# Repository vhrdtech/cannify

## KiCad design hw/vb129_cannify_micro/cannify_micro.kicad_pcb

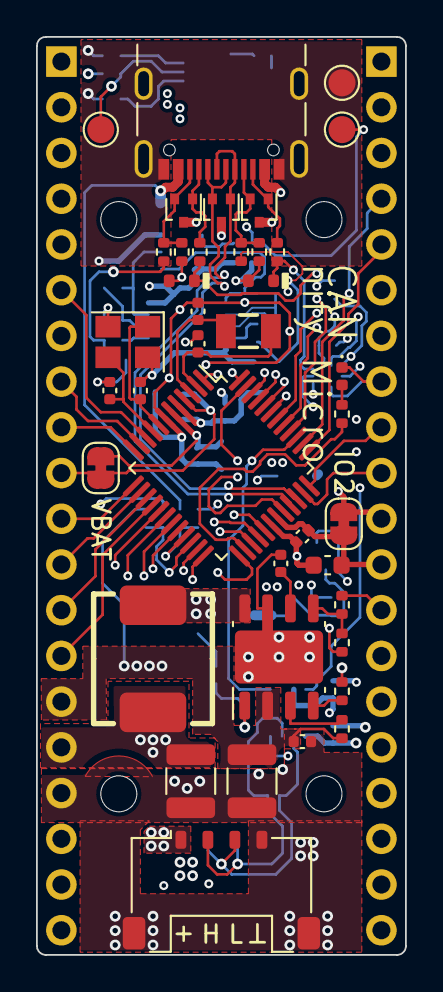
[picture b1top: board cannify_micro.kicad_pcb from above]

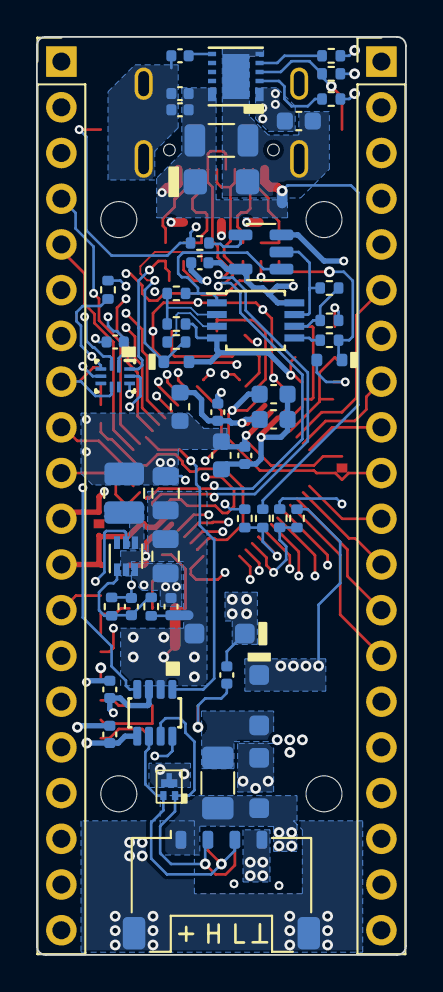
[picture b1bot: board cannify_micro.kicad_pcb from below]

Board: 6 copper layers, 20.5 x 51.0 mm, 98 parts (55 on the bottom side), 83 nets.

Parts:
C1, C2: 10nF; C_0402_1005Metric
C5: 10uF; C_1210_3225Metric
C6, C7, C8, C11, C17, C18, C19, C22, C23, C24, C27: 100nF; C_0402_1005Metric
C9: 100uF; C_1210_3225Metric
C10, C13: 10uF; C_0805_2012Metric
C12: DNP; C_0402_1005Metric
C14: 10uF; C_1206_3216Metric
C15: 3.3nF; C_0402_1005Metric
C16: DNP; C_0603_1608Metric
C20, C25: 4.7uF; C_0603_1608Metric
C21, C31: 24pF; C_0402_1005Metric
C26, C28: 1uF; C_0603_1608Metric
C29, C30: 12pF; C_0402_1005Metric
D1, D2, D3: ESD; SOT-416
D4: Vbr=24V Vcl=35V; D_SMF
D5, D12: Schottky 3A; D_SOD-123F
D6, D7, D8, D9: 5V6; D_SOD-523
D10: PESD2CANFD24V-QBZ; DFN1110D-3_3-XDFN
D11: Vbr=56V; TVS_SOD-123F
D14: LED; LED_0402_1005Metric
F1: 4A Slow blow; Fuse_1206_3216Metric
FB1: MH1608-601Y; L_0603_1608Metric
H1, H2, H3, H4: MountingHole; MountingHole_2.2mm_M2
J1, J2: Conn_01x20; PinHeader_1x20_P2.54mm_Vertical
J3: USB_C_Receptacle_USB2.0; USB_C_Receptacle_GCT_USB4105-xx-A_16P_TopMnt_Horizontal
J4, J5: Pico-Lock 4P; Molex_Pico-Lock_504050-0491_1x04-1MP_P1.50mm_Horizontal
JP2, JP3: Jumper (Short); SolderJumper-2_P1.3mm_Bridged_RoundedPad1.0x1.5mm
L1: LMLP07A7M8R2DTAS; LMLP07A7
L2: DFE252010F-1R0M=P2; L_1008_2520Metric
R1, R2, R18, R19, R20, R21: 5K1; R_0402_1005Metric
R3: 16K2; R_0402_1005Metric
R4, R27, R31: 1K69; R_0402_1005Metric
R5: 49K9; R_0402_1005Metric
R6, R8, R23, R24, R28: 10K; R_0402_1005Metric
R7: 57K6; R_0402_1005Metric
R10: 45k; R_0402_1005Metric
R11: 10k; R_0402_1005Metric
R12, R25: 0; R_0402_1005Metric
R13: 301K; R_0402_1005Metric
R14: 100K; R_0402_1005Metric
R15, R16, R17, R22: 200; R_0402_1005Metric
R30: 39K2; R_0402_1005Metric
TP1, TP2, TP5: TestPoint_Probe; TestPoint_Pad_D1.5mm
U1: STM32G0B1CETxN; LQFP-48_7x7mm_P0.5mm
U2: LV14360SDDAR; SOIC-8-1EP_TI_NOVIA
U3: RT5760; SOT-563
U4: AOZ1376DI-02; DFN-12-AOZ
U5: LMV358A; TSSOP-8_3x3mm_P0.65mm
U6: 74LVC1G08; SOT-23-5
U7: TS3A5223RSWR; RSW0010A
U8: TCAN1044VDDF; TSOT23-6-TI-DDF0008A
Y1: 32.768kHz; ECX-.327-CDX-1293
Y2: 12MHz; Crystal_SMD_3225-4Pin_3.2x2.5mm

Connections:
+3V3_DCDC: C12.1, C13.1, C17.1, C18.1, C19.1, C20.1, C23.1, FB1.1, J2.11, JP2.1 (A), JP3.2 (B), L2.2, R10.2, U1.6 (VDD), U5.8 (V+), U6.5 (VCC), U7.1 (VCC), U8.5 (VIO)
+5V0_DCDC: C9.1, C10.1, C11.1, C16.1, C22.1, J1.16, L1.2, R7.2, R14.2, U3.3 (VIN), U3.5 (EN), U4.1 (VOUT), U4.2 (VOUT), U8.3 (VCC)
+VIN_CAN: C5.1, C6.1, D12.1 (K), J1.15, R6.1, R30.1, U2.2 (VIN)
+VIN_USB: C1.1, C2.1, C14.1, D4.1 (A1), J3.A4 (VBUS), J3.A9 (VBUS), J3.B4 (VBUS), J3.B9 (VBUS), R3.1, U4.11 (VIN), U4.12 (VIN)
/3V3_FB: C12.2, R10.1, R11.2, U3.1 (FB)
/3V3_SW: L2.1, U3.4 (SW)
/+VCAN_F: D12.2 (A), F1.2
/+VCAN_J: D11.2 (A2), F1.1, J4.1, J5.1
/+VDDIO2: C24.1, C25.1, J2.12, JP3.1 (A), U1.31 (VDDIO2)
/AOZ_ENB: R12.1, U4.5 (ENB)
/AOZ_POVP: R13.1, U4.3 (POVP)
/AOZ_SS: C15.1, U4.7 (SS)
/CANH: D10.1 (A1), J4.2, J5.2, U8.7 (CANH)
/CANL: D10.2 (A2), J4.3, J5.3, U8.6 (CANL)
/CAN_STBY: U1.1 (PC13), U8.8 (STB)
/CAN_VDIV: R30.2, R31.1, U1.22 (PB10)
/CC1: D2.2 (K2), J3.A5 (CC1), R1.2, R15.1
/CC1_PR: D6.1 (K), R15.2, R18.1
/CC2: D1.2 (K2), J3.B5 (CC2), R2.2, R16.1
/CC2_PR: D7.1 (K), R16.2, R20.1
/FDCAN_RX: U1.47 (PB8), U8.4 (RXD)
/FDCAN_TX: U1.39 (PD1), U8.1 (TXD)
/HF_OSC_IN: C31.1, U1.8 (PF0), Y2.1
/HF_OSC_OUT: C21.1, U1.9 (PF1), Y2.3
/LED: R27.2, U1.26 (PB14)
/LF_OSC_IN: C29.1, U1.2 (PC14), Y1.1
/LF_OSC_OUT: C30.1, U1.3 (PC15), Y1.2
/LV_BOOT: C8.1, U2.1 (BOOT)
/LV_EN: R6.2, U2.3 (EN)
/LV_FB: R7.1, R8.2, U2.5 (FB)
/LV_RT: R5.1, U2.4 (RT/SYNC)
/LV_SS: C7.1, U2.6 (SS)
/LV_SW: C8.2, D5.1 (K), L1.1, U2.8 (SW)
/PA0: J1.8, U1.11 (PA0)
/PA1: J1.9, U1.12 (PA1)
/PA2: J1.11, U1.13 (PA2)
/PA3: J1.12, U1.14 (PA3)
/PA4: J1.13, U1.15 (PA4)
/PA5: J1.14, U1.16 (PA5)
/PA6: J1.18, U1.17 (PA6)
/PA7: J1.19, U1.18 (PA7)
/PA8: J2.15, U1.28 (PA8)
/PA9: J2.14, U1.29 (PA9/UCPD1_DBCC1)
/PA10: J2.6, U1.32 (PA10/UCPD1_DBCC2)
/PA15: J2.5, U1.37 (PA15)
/PB0: J1.20, U1.19 (PB0)
/PB1: J2.20, U1.20 (PB1)
/PB3: J2.1, U1.42 (PB3)
/PB4: J1.1, U1.43 (PB4)
/PB5: J1.2, U1.44 (PB5)
/PB6: J1.3, U1.45 (PB6)
/PB7: J1.4, U1.46 (PB7)
/PB9: J1.5, U1.48 (PB9)
/PB11: J2.19, U1.23 (PB11)
/PB12: J2.18, U1.24 (PB12)
/PB13: J2.17, U1.25 (PB13)
/PB15: J2.16, U1.27 (PB15)
/PD0: J2.4, U1.38 (PD0)
/PD2: J2.3, U1.40 (PD2)
/PD3: J2.2, U1.41 (PD3)
/PF2_NRST: J1.6, U1.10 (PF2)
/SBU1: D1.1 (K1), J3.A8 (SBU1), R17.1
/SBU1_PR: D8.1 (K), R17.2, U7.2 (NO1)
/SBU2: D2.1 (K1), J3.B8 (SBU2), R22.1
/SBU2_PR: D9.1 (K), R22.2, U7.10 (NO2)
/SWCLK: J2.9, R28.2, U1.36 (PA14), U7.3 (COM1)
/SWDIO: J2.10, U1.35 (PA13), U7.9 (COM2)
/SWD_SEL: R25.2, TP1.1, U7.4 (SEL1), U7.8 (SEL2)
/USB_N: D3.1 (K1), J3.A7 (D-), J3.B7 (D-), U1.33 (PA11/PA9)
/USB_P: D3.2 (K2), J3.A6 (D+), J3.B6 (D+), U1.34 (PA12/PA10)
/USB_VDIV: R3.2, R4.1, U1.21 (PB2)
/VBAT: C26.1, J1.10, JP2.2 (B), U1.4 (VBAT)
/VUSB_FLTB: R14.1, TP2.1, U4.4 (FLTB)
GND: C1.2, C2.2, C5.2, C6.2, C7.2, C9.2, C10.2, C11.2, C13.2, C14.2, C15.2, C16.2, C17.2, C18.2, C19.2, C20.2, C21.2, C22.2, C23.2, C24.2, C25.2, C26.2, C27.2, C28.2, C29.2, C30.2, C31.2, D1.3 (A), D2.3 (A), D3.3 (A), D4.2 (A2), D5.2 (A), D6.2 (A), D7.2 (A), D8.2 (A), D9.2 (A), D10.3 (common), D11.1 (A1), D14.1 (K), J1.7, J1.17, J2.8, J2.13, J3.A1 (GND), J3.A12 (GND), J3.B1 (GND), J3.B12 (GND), J3.S1 (SHIELD), J4.4, J4.MP (MountPin), J5.4, J5.MP (MountPin), R1.1, R2.1, R4.2, R5.2, R8.1, R11.1, R12.2, R13.2, R19.1, R21.1, R28.1, R31.2, TP5.1, U1.7 (VSS), U1.30 (VSS), U2.7 (GND), U2.9 (EPAD_GND), U3.2 (GND), U4.6 (GND), U4.13 (EP_GND), U5.4 (V-), U6.3 (GND), U7.6 (GND), U8.2 (GND), Y2.2, Y2.4
unnamed: D14.2 (A), R27.1
unnamed: R23.2, U5.1, U6.1
unnamed: R24.2, U5.7, U6.2
unnamed: R25.1, U6.4
unnamed: C27.1, C28.1, FB1.2, U1.5 (VREF+)
unnamed: R18.2, U5.3 (+)
unnamed: R19.2, R23.1, U5.2 (-)
unnamed: R20.2, U5.5 (+)
unnamed: R21.2, R24.1, U5.6 (-)

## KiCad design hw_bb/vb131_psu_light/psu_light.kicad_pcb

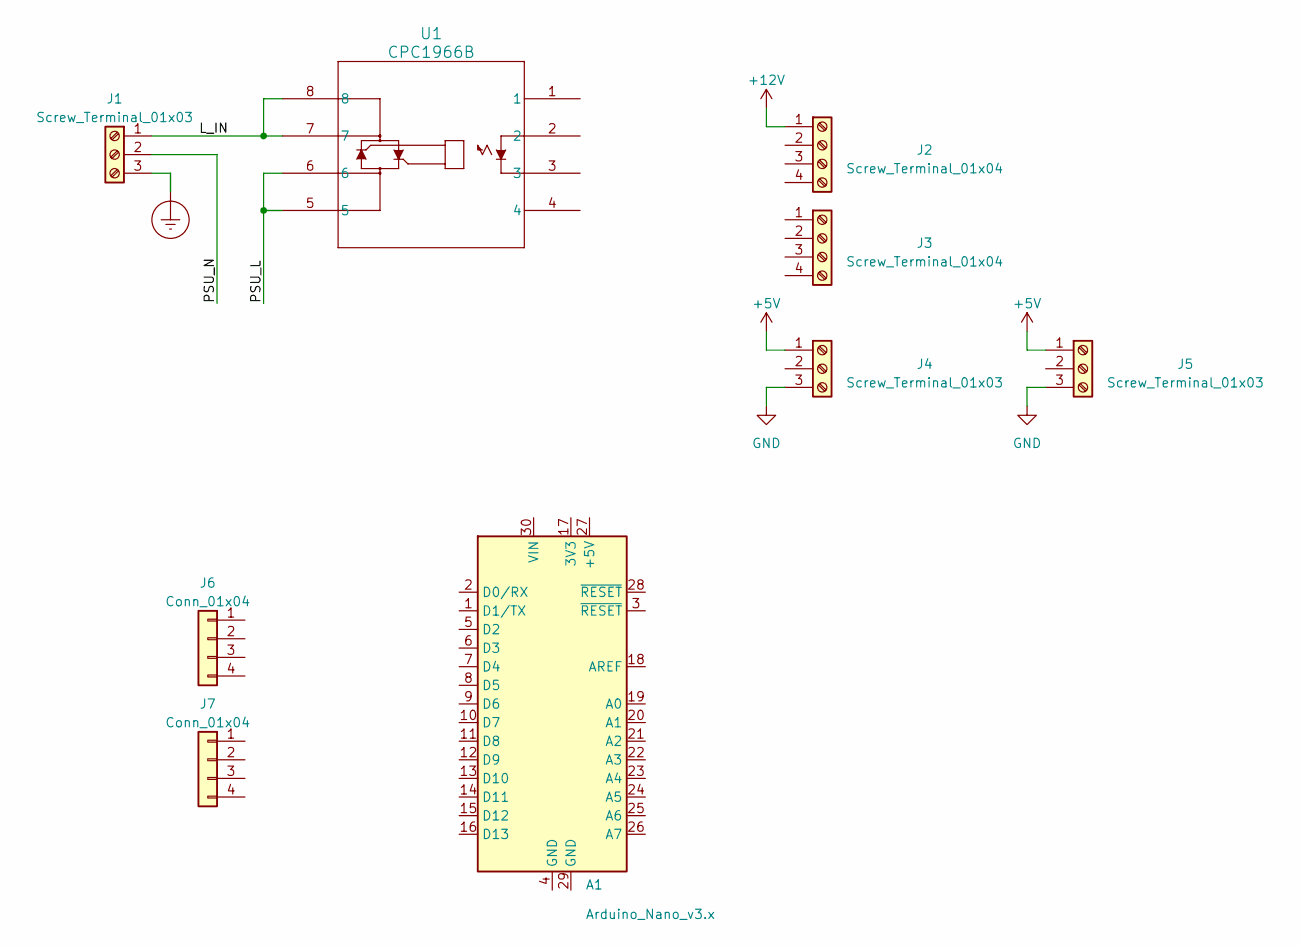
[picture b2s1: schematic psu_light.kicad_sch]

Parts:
A1: Arduino_Nano_v3.x; Arduino_Nano
J1: Screw_Terminal_01x03; TerminalBlock_Phoenix_PT-1,5-3-5.0-H_1x03_P5.00mm_Horizontal
J2, J3: Screw_Terminal_01x04; TerminalBlock_Phoenix_PT-1,5-4-3.5-H_1x04_P3.50mm_Horizontal
J4, J5: Screw_Terminal_01x03; TerminalBlock_Phoenix_PT-1,5-3-3.5-H_1x03_P3.50mm_Horizontal
J6, J7: Conn_01x04; Molex_Nano-Fit_105309-xx04_1x04_P2.50mm_Vertical
U1: CPC1966B; CPC1966B_IXYS-M

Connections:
+5V: J4.1, J5.1
+12V: J2.1
/L_IN: J1.1, U1.7, U1.8
/PSU_L: U1.5, U1.6
/PSU_N: J1.2
Earth_Protective: J1.3
GND: J4.3, J5.3

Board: 2 copper layers, 9 parts (0 on the bottom side), 4 nets, no tracks yet.

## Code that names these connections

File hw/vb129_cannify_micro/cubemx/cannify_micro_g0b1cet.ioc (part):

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Mcu.Name=STM32G0B1C(B-C-E)TxN
Mcu.Package=LQFP48
Mcu.UserName=STM32G0B1CETxN
PA10.Mode=EnableDeadBattery
PA10.Signal=UCPD1_DBCC2
PA11\ [PA9].Mode=Device
PA11\ [PA9].Signal=USB_DM
PA12\ [PA10].Mode=Device
PA12\ [PA10].Signal=USB_DP
PA13.Mode=Serial_Wire
PA13.Signal=SYS_SWDIO
PA14-BOOT0.Mode=Serial_Wire
PA14-BOOT0.Signal=SYS_SWCLK
PA15.Mode=Clock-out-2
PA15.Signal=RCC_MCO_2
PA8.Mode=Dual_Role_AllSignals
PA8.Signal=UCPD1_CC1
PA9.Mode=EnableDeadBattery
PA9.Signal=UCPD1_DBCC1
PB10.GPIOParameters=GPIO_Label
PB10.GPIO_Label=CAN_VDIV
PB10.Mode=IN11
PB10.Signal=ADC1_IN11
PB13.GPIOParameters=GPIO_Label
PB13.GPIO_Label=VUSB_FLTB
PB13.Signal=GPIO_Input
PB14.GPIOParameters=GPIO_Label
PB14.GPIO_Label=LED
PB14.Signal=S_TIM15_CH1
PB15.Mode=Dual_Role_AllSignals
PB15.Signal=UCPD1_CC2
PB2.GPIOParameters=GPIO_Label
PB2.GPIO_Label=USB_VDIV
PB2.Mode=IN10
PB2.Signal=ADC1_IN10
PC13.GPIOParameters=GPIO_Label
PC13.GPIO_Label=CAN_STBY
PC13.Signal=GPIO_Output
PC14-OSC32_IN\ (PC14).Mode=LSE-External-Oscillator
PC14-OSC32_IN\ (PC14).Signal=RCC_OSC32_IN
PC15-OSC32_OUT\ (PC15).Mode=LSE-External-Oscillator
PC15-OSC32_OUT\ (PC15).Signal=RCC_OSC32_OUT
PD0.Mode=FDCAN_Activate
PD0.Signal=FDCAN1_RX
PD1.Mode=FDCAN_Activate
PD1.Signal=FDCAN1_TX
PD3.GPIOParameters=GPIO_Label
PD3.GPIO_Label=NC
PD3.Signal=GPIO_Input
PF0-OSC_IN\ (PF0).Mode=HSE-External-Oscillator
PF0-OSC_IN\ (PF0).Signal=RCC_OSC_IN
PF1-OSC_OUT\ (PF1).Mode=HSE-External-Oscillator
PF1-OSC_OUT\ (PF1).Signal=RCC_OSC_OUT
RCC.HSE_VALUE=8000000
RCC.SYSCLKFreq_VALUE=16000000
board=custom

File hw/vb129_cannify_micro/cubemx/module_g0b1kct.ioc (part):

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Mcu.Name=STM32G0B1K(B-C-E)Tx
Mcu.Package=LQFP32
Mcu.UserName=STM32G0B1KCTx
PA0.Mode=IN0
PA0.Signal=ADC1_IN0
PA11\ [PA9].Mode=Device
PA11\ [PA9].Signal=USB_DM
PA12\ [PA10].Mode=Device
PA12\ [PA10].Signal=USB_DP
PA13.Mode=Serial_Wire
PA13.Signal=SYS_SWDIO
PA14-BOOT0.Mode=Serial_Wire
PA14-BOOT0.Signal=SYS_SWCLK
PB0.Mode=FDCAN_Activate
PB0.Signal=FDCAN2_RX
PB1.Mode=FDCAN_Activate
PB1.Signal=FDCAN2_TX
PB2.Mode=IN10
PB2.Signal=ADC1_IN10
PB8.Mode=FDCAN_Activate
PB8.Signal=FDCAN1_RX
PB9.Mode=FDCAN_Activate
PB9.Signal=FDCAN1_TX
PC14-OSC32_IN\ (PC14).Mode=HSE-External-Clock-Source
PC14-OSC32_IN\ (PC14).Signal=RCC_OSC_IN
PC15-OSC32_OUT\ (PC15).Mode=OSC enable
PC15-OSC32_OUT\ (PC15).Signal=RCC_OSC_EN
PF2-NRST.Mode=Clock-out
PF2-NRST.Signal=RCC_MCO
RCC.HSE_VALUE=8000000
RCC.SYSCLKFreq_VALUE=16000000
board=custom

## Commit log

2023-11-30 Draw CANnify Micro schematics and do pre-placement on the PCB.
2023-12-17 Add VB131 PSU Light controller baseboard.
2023-12-31 Layout done.
